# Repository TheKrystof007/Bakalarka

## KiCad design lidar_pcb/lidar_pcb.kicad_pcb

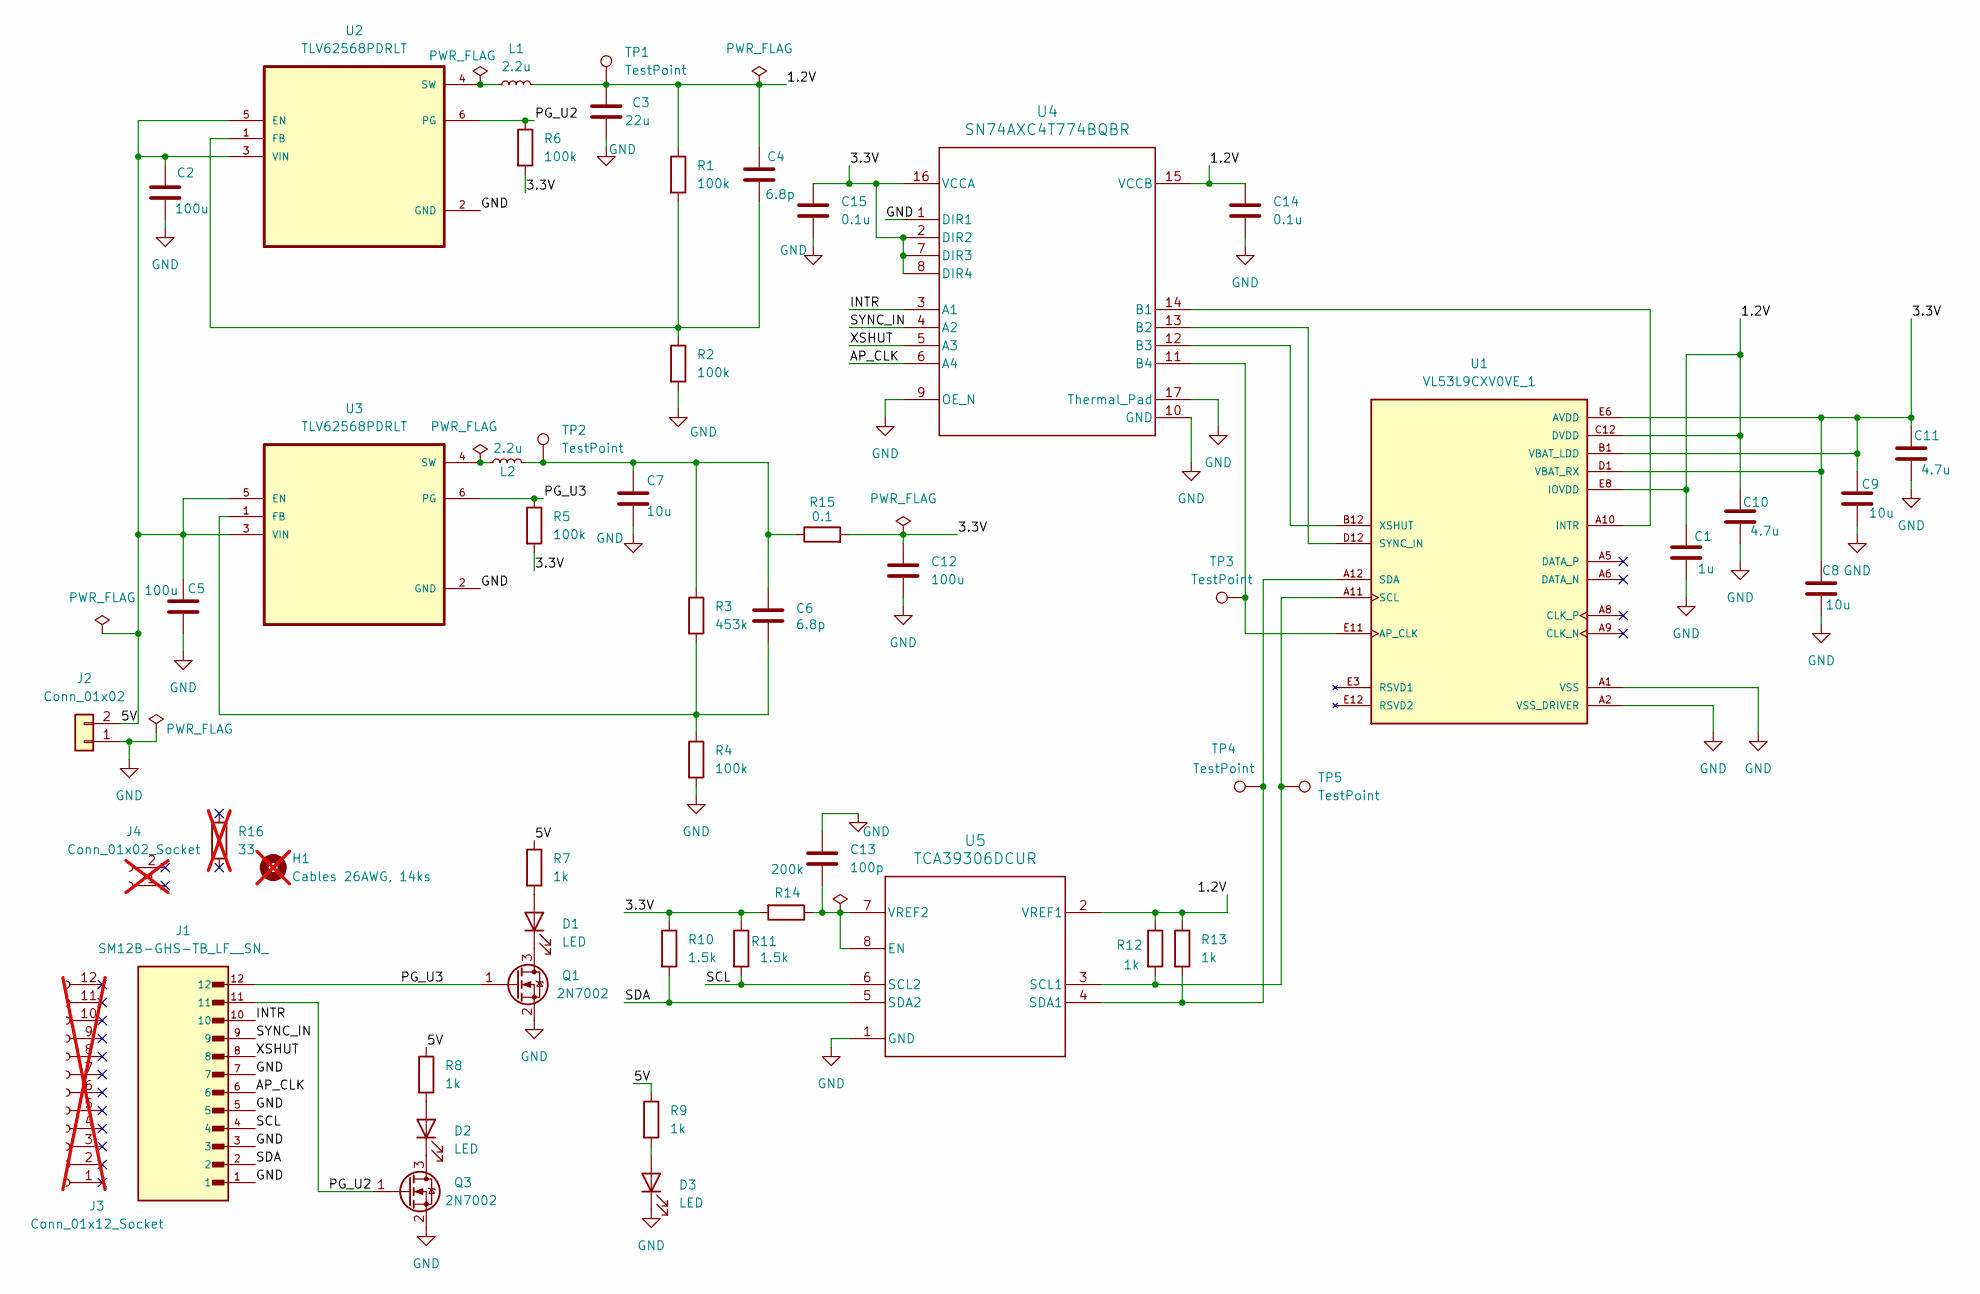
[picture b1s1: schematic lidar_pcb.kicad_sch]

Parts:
C1: 1u; C_0603_1608Metric
C2, C5, C12: 100u; C_1206_3216Metric
C3: 22u; C_0805_2012Metric
C4, C6: 6.8p; C_0603_1608Metric
C7, C8, C9: 10u; C_0805_2012Metric
C10, C11: 4.7u; C_0603_1608Metric
C13: 100p; C_0603_1608Metric
C14, C15: 0.1u; C_0603_1608Metric
D1, D2, D3: LED; LED_0603_1608Metric
H1: Cables 26AWG, 14ks; not fitted
J1: SM12B-GHS-TB_LF__SN_; JST_SM12B-GHS-TB_LF__SN_
J2: Conn_01x02; JST_GH_SM02B-GHS-TB_1x02-1MP_P1.25mm_Horizontal
J3: Conn_01x12_Socket; not fitted
J4: Conn_01x02_Socket; not fitted
L1, L2: 2.2u; L_1008_2520Metric
Q1, Q3: 2N7002; SOT-23
R1, R2, R4, R5, R6: 100k; R_0603_1608Metric
R3: 453k; R_0603_1608Metric
R7, R8, R9, R12, R13: 1k; R_0603_1608Metric
R10, R11: 1.5k; R_0603_1608Metric
R14: 200k; R_0603_1608Metric
R15: 0.1; R_0805_2012Metric
R16: 33; not fitted
TP1, TP2, TP3, TP4, TP5: TestPoint; TestPoint_Keystone_5015_Micro-Minature
U1: VL53L9CXV0VE_1; XDCR_VL53L9CXV0VE_1; PARTREV 7
U2, U3: TLV62568PDRLT; SOT50P160X60-6N
U4: SN74AXC4T774BQBR; BQB0016A-MFG
U5: TCA39306DCUR; DCU0008A-IPC_A

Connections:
/1.2V: C1.1, C3.1, C4.1, C10.1, C14.1, L1.2, R1.1, R12.1, R13.1, TP1.1, U1.C12 (DVDD), U1.E8 (IOVDD), U4.15 (VCCB), U5.2 (VREF1)
/5V: C2.1, C5.1, J2.2, R7.1, R8.1, R9.1, U2.3 (VIN), U2.5 (EN), U3.3 (VIN), U3.5 (EN)
/AP_CLK: J1.6, U4.6 (A4)
/INTR: J1.10, U4.3 (A1)
/PG_U2: J1.11, Q3.1 (G), R6.1, U2.6 (PG)
/PG_U3: J1.12, Q1.1 (G), R5.1, U3.6 (PG)
/SCL: J1.4, R11.2, U5.6 (SCL2)
/SDA: J1.2, R10.2, U5.5 (SDA2)
/SYNC_IN: J1.9, U4.4 (A2)
/XSHUT: J1.8, U4.5 (A3)
AVDD: C8.1, C9.1, C11.1, C12.1, C15.1, R5.2, R6.2, R10.1, R11.1, R14.2, R15.2, U1.B1 (VBAT_LDD), U1.D1 (VBAT_RX), U1.E6 (AVDD), U1.E7 (AVDD), U4.2 (DIR2), U4.7 (DIR3), U4.8 (DIR4), U4.16 (VCCA)
GND: C1.2, C2.2, C3.2, C5.2, C7.2, C8.2, C9.2, C10.2, C11.2, C12.2, C13.1, C14.2, C15.2, D3.1 (K), J1.1, J1.3, J1.5, J1.7, J2.1, Q1.2 (S), Q3.2 (S), R2.2, R4.2, U1.A1 (VSS), U1.A2 (VSS_DRIVER), U1.A3 (VSS_DRIVER), U1.A4 (VSS), U1.A7 (VSS), U1.B4 (VSS), U1.B5 (VSS), U1.B6 (VSS), U1.B7 (VSS), U1.B8 (VSS), U1.B9 (VSS), U1.C1 (VSS), U1.D4 (VSS), U1.D5 (VSS), U1.D6 (VSS), U1.D7 (VSS), U1.D8 (VSS), U1.D9 (VSS), U1.E1 (VSS), U1.E2 (VSS), U1.E4 (VSS), U1.E5 (VSS), U1.E9 (VSS), U1.E10 (VSS), U2.2 (GND), U3.2 (GND), U4.1 (DIR1), U4.9 (OE_N), U4.10 (GND), U4.17 (Thermal_Pad), U4.18, U4.19, U5.1 (GND)
unnamed: C6.1, C7.1, L2.2, R3.1, R15.1, TP2.1
unnamed: D1.2 (A), R7.2
unnamed: D1.1 (K), Q1.3 (D)
unnamed: D2.2 (A), R8.2
unnamed: D2.1 (K), Q3.3 (D)
unnamed: D3.2 (A), R9.2
unnamed: TP3.1, U1.E11 (AP_CLK), U4.11 (B4)
unnamed: U1.A10 (INTR), U4.14 (B1)
unnamed: R12.2, TP5.1, U1.A11 (SCL), U5.3 (SCL1)
unnamed: R13.2, TP4.1, U1.A12 (SDA), U5.4 (SDA1)
unnamed: U1.D12 (SYNC_IN), U4.13 (B2)
unnamed: U1.B12 (XSHUT), U4.12 (B3)
unnamed: C4.2, R1.2, R2.1, U2.1 (FB)
unnamed: L1.1, U2.4 (SW)
unnamed: C6.2, R3.2, R4.1, U3.1 (FB)
unnamed: L2.1, U3.4 (SW)
unnamed: C13.2, R14.1, U5.7 (VREF2), U5.8 (EN)

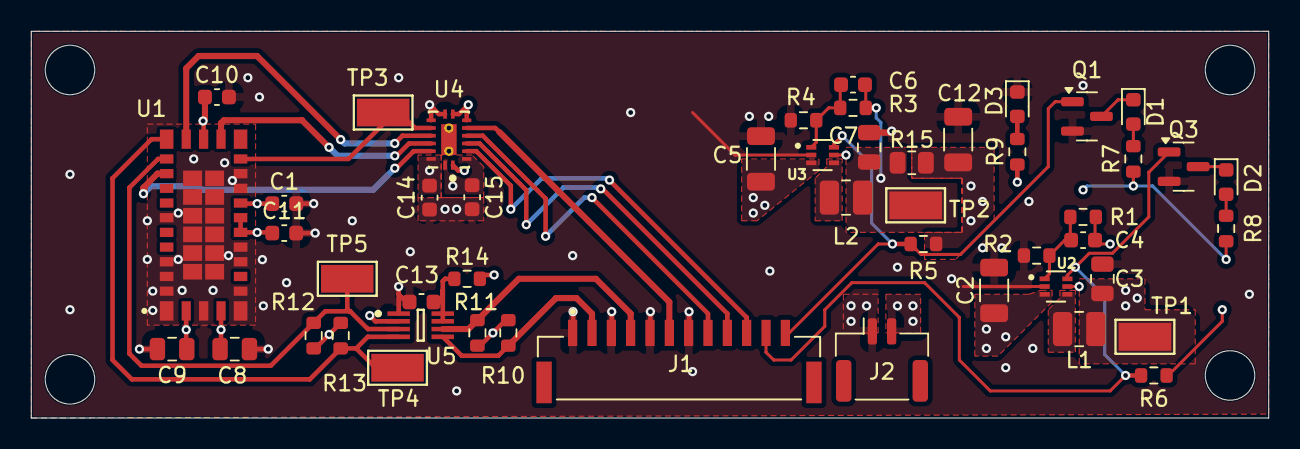
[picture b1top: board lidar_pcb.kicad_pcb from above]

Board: 4 copper layers, 80.0 x 25.0 mm, 49 parts (0 on the bottom side), 29 nets.

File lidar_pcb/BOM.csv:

"Reference","Value","Qty","MANUFACTURER","MP","Purchase-URL","Footprint","DNP","Datasheet"
"C1","1u","1","Murata Electronics","GRM188R71C105KA12D","https://mou.sr/4eRtQ5U","Capacitor_SMD:C_0603_1608Metric","","~"
"C2","100u","1","Murata Electronics","GRM31CR61A107MEA8L","https://mou.sr/4i4um2L","Capacitor_SMD:C_1206_3216Metric","","~"
"C3","22u","1","Murata Electronics","GRM21BR61C226ME44L","https://mou.sr/3UMbgW8","Capacitor_SMD:C_0805_2012Metric","","~"
"C4","6.8p","1","Murata Electronics","GRM1885C1H6R8CA01D","https://mou.sr/4ik3yKA","Capacitor_SMD:C_0603_1608Metric","","~"
"C5","100u","1","Murata Electronics","GRM31CR61A107MEA8L","https://mou.sr/4i4um2L","Capacitor_SMD:C_1206_3216Metric","","~"
"C6","6.8p","1","Murata Electronics","GRM1885C1H6R8CA01D","https://mou.sr/4ik3yKA","Capacitor_SMD:C_0603_1608Metric","","~"
"C7","10u","1","Murata Electronics","GRM21BR71C106KE15L","https://mou.sr/4yFdDb6","Capacitor_SMD:C_0805_2012Metric","","~"
"C8","10u","1","Murata Electronics","GRM21BR71C106KE15L","https://mou.sr/4yFdDb6","Capacitor_SMD:C_0805_2012Metric","","~"
"C9","10u","1","Murata Electronics","GRM21BR71C106KE15L","https://mou.sr/4yFdDb6","Capacitor_SMD:C_0805_2012Metric","","~"
"C10","4.7u","1","Murata Electronics","GRM188R61C475KAAJD","https://mou.sr/4BpDC9f","Capacitor_SMD:C_0603_1608Metric","","~"
"C11","4.7u","1","Murata Electronics","GRM188R61C475KAAJD","https://mou.sr/4BpDC9f","Capacitor_SMD:C_0603_1608Metric","","~"
"C12","100u","1","Murata Electronics","GRM31CR61A107MEA8L","https://mou.sr/4i4um2L","Capacitor_SMD:C_1206_3216Metric","","~"
"C13","100p","1","Murata Electronics","GRM1885C1H101JA01D","https://mou.sr/4zS5LEf","Capacitor_SMD:C_0603_1608Metric","","~"
"C14","0.1u","1","Murata Electronics","GRM188R71H104KA93D","https://mou.sr/4dTQiLA","Capacitor_SMD:C_0603_1608Metric","","~"
"C15","0.1u","1","Murata Electronics","GRM188R71H104KA93D","https://mou.sr/4dTQiLA","Capacitor_SMD:C_0603_1608Metric","","~"
"D1","LED","1","LITEON","LTST-C190KRKT","https://mou.sr/4khCUVf","LED_SMD:LED_0603_1608Metric","","~"
"D2","LED","1","LITEON","LTST-C190KSKT","https://mou.sr/4ihjCg2","LED_SMD:LED_0603_1608Metric","","~"
"D3","LED","1","LITEON","LTST-C190KGKT","https://mou.sr/4iHxBwf","LED_SMD:LED_0603_1608Metric","","~"
"H1","Cables 26AWG, 14ks","1","JST Commercial","AGHDGHD26K305","https://mou.sr/3U1hql3","","DNP","~"
"J1","SM12B-GHS-TB_LF__SN_","1","JST Commercial","SM12B-GHS-TB(LF)(SN)","https://mou.sr/47Ee22E","kicad_GH_12pin_konektor:JST_SM12B-GHS-TB_LF__SN_","",""
"J2","Conn_01x02","1","JST Commercial","SM02B-GHS-TB(LF)(SN)","https://mou.sr/3Wqv9m4","Connector_JST:JST_GH_SM02B-GHS-TB_1x02-1MP_P1.25mm_Horizontal","","~"
"J3","Conn_01x12_Socket","1","JST Commercial","GHR-12V-S","https://mou.sr/4spyhL3","","DNP","~"
"J4","Conn_01x02_Socket","1","JST Commercial","GHR-02V-S","https://mou.sr/4st0CjI","","DNP","~"
"L1","2.2u","1","Murata Electronics","DFE252012F-2R2M=P2","https://mou.sr/4i2VgYO","Inductor_SMD:L_1008_2520Metric","","~"
"L2","2.2u","1","Murata Electronics","DFE252012F-2R2M=P2","https://mou.sr/4i2VgYO","Inductor_SMD:L_1008_2520Metric","","~"
"Q1","2N7002","1","onsemi","2N7002","https://mou.sr/4zXxaF4","Package_TO_SOT_SMD:SOT-23","","https://www.onsemi.com/pub/Collateral/NDS7002A-D.PDF"
"Q3","2N7002","1","onsemi","2N7002","https://mou.sr/4zXxaF4","Package_TO_SOT_SMD:SOT-23","","https://www.onsemi.com/pub/Collateral/NDS7002A-D.PDF"
"R1","100k","1","YAGEO","RC0603FR-07100KL","https://mou.sr/4BIYvMX","Resistor_SMD:R_0603_1608Metric","","~"
"R2","100k","1","YAGEO","RC0603FR-07100KL","https://mou.sr/4BIYvMX","Resistor_SMD:R_0603_1608Metric","","~"
"R3","453k","1","YAGEO","RC0603FR-07453KL","https://mou.sr/3WqwTf6","Resistor_SMD:R_0603_1608Metric","","~"
"R4","100k","1","YAGEO","RC0603FR-07100KL","https://mou.sr/4BIYvMX","Resistor_SMD:R_0603_1608Metric","","~"
"R5","100k","1","YAGEO","RC0603FR-07100KL","https://mou.sr/4BIYvMX","Resistor_SMD:R_0603_1608Metric","","~"
"R6","100k","1","YAGEO","RC0603FR-07100KL","https://mou.sr/4BIYvMX","Resistor_SMD:R_0603_1608Metric","","~"
"R7","1k","1","YAGEO","RC0603FR-071KL","https://mou.sr/4zTccqG","Resistor_SMD:R_0603_1608Metric","","~"
"R8","1k","1","YAGEO","RC0603FR-071KL","https://mou.sr/4zTccqG","Resistor_SMD:R_0603_1608Metric","","~"
"R9","1k","1","YAGEO","RC0603FR-071KL","https://mou.sr/4zTccqG","Resistor_SMD:R_0603_1608Metric","","~"
"R10","1.5k","1","YAGEO","RC0603FR-071K5L","https://mou.sr/4ipKQS6","Resistor_SMD:R_0603_1608Metric","","~"
"R11","1.5k","1","YAGEO","RC0603FR-071K5L","https://mou.sr/4ipKQS6","Resistor_SMD:R_0603_1608Metric","","~"
"R12","1k","1","YAGEO","RC0603FR-071KL","https://mou.sr/4zTccqG","Resistor_SMD:R_0603_1608Metric","","~"
"R13","1k","1","YAGEO","RC0603FR-071KL","https://mou.sr/4zTccqG","Resistor_SMD:R_0603_1608Metric","","~"
"R14","200k","1","YAGEO","RC0603FR-07200KL","https://mou.sr/4zQZYPc","Resistor_SMD:R_0603_1608Metric","","~"
"R15","0.1","1","YAGEO","RL0805FR-070R1L","https://mou.sr/4BpNI9X","Resistor_SMD:R_0805_2012Metric","","~"
"TP1","TestPoint","1","Keystone Electronics","5015","https://mou.sr/4i7C63V","TestPoint:TestPoint_Keystone_5015_Micro-Minature","","~"
"TP2","TestPoint","1","Keystone Electronics","5015","https://mou.sr/4i7C63V","TestPoint:TestPoint_Keystone_5015_Micro-Minature","","~"
"TP3","TestPoint","1","Keystone Electronics","5015","https://mou.sr/4i7C63V","TestPoint:TestPoint_Keystone_5015_Micro-Minature","","~"
"TP4","TestPoint","1","Keystone Electronics","5015","https://mou.sr/4i7C63V","TestPoint:TestPoint_Keystone_5015_Micro-Minature","","~"
"TP5","TestPoint","1","Keystone Electronics","5015","https://mou.sr/4i7C63V","TestPoint:TestPoint_Keystone_5015_Micro-Minature","","~"
"U1","VL53L9CXV0VE_1","1","STMicroelectronics","VL53L9CXV0VE/1","https://www.snapeda.com/api/url_track_click_mouser/?unipart_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","kicad_lidar:XDCR_VL53L9CXV0VE_1","",""
"U2","TLV62568PDRLT","1","Texas Instruments","TLV62568PDRLT","https://mou.sr/4zea2C4","kicad_buck:SOT50P160X60-6N","",""
"U3","TLV62568PDRLT","1","Texas Instruments","TLV62568PDRLT","https://mou.sr/4zea2C4","kicad_buck:SOT50P160X60-6N","",""
"U4","SN74AXC4T774BQBR","1","Texas Instruments","SN74AXC4T774BQBR","https://mou.sr/4eRsOa2","kicad_4pin_logic_convertor:BQB0016A-MFG","","https://www.ti.com/lit/gpn/sn74axc4t774"
"U5","TCA39306DCUR","1","Texas Instruments","TCA39306DCUR","https://mou.sr/4zNttBt","kicad_2pin_logic_convertor:DCU0008A-IPC_A","","https://www.ti.com/lit/gpn/tca39306"
